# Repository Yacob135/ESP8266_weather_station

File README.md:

# ESP8266_weather_station

This weather station has an ESP8266-12F in combination with DS18B20 and/or BME280 for sensing. I used a TP4056 module for 18650 Li-Ion battery charging/protection and TPS63900 buck-boost converter, which has incredibly low quiescent current combined with great efficiency at low power consumption (>90% at 10uA).

The station connects to my local Blynk server and sends the data every 5 minutes. During deep-sleep the whole circuit consumes about 25uA, which is fantastic. It should last about a year on one charge, since it connects to my server, sends the data and goes back to sleep in about 0.7s on average (I used Blynk API to reduce the connection time). So the overall power consumption is really low.

Just a little warning when buying ESP8266-12F modules from aliexpress. Make sure to buy the Ai-Thinker version, since the "Espressif" version will have about 150uA in deep-sleep instead of 20uA. Learnt this the hard way.

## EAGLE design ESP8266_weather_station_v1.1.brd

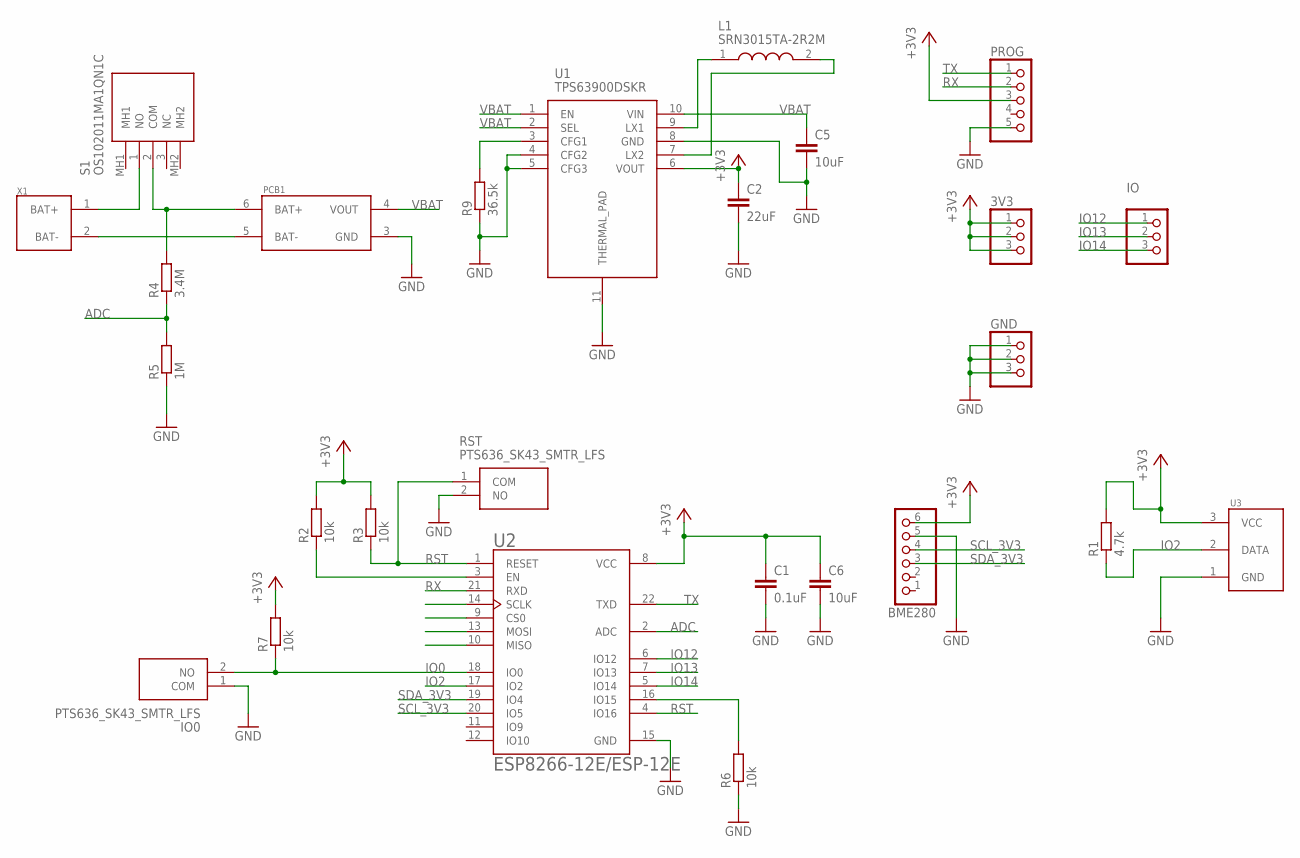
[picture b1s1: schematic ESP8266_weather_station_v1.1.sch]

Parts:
3V3: PINHD-1X3; 1X03
BME280: PINHD-1X6; 1X06
C1: 0.1uF; C0805
C2: 22uF; C0805
C5, C6: 10uF; C0805
GND: PINHD-1X3; 1X03
IO: PINHD-1X3; 1X03
IO0: PTS636_SK43_SMTR_LFS; PTS636SK43SMTRLFS
L1: SRN3015TA-2R2M; SRN3015TA2R2M
PCB1: TP4056_MODULE
PROG: PINHD-1X5; 1X05
R1: 4.7k; R0805
R2, R3, R6, R7: 10k; R0805
R4: 3.4M; R0805
R5: 1M; R0805
R9: 36.5k; R0805
RST: PTS636_SK43_SMTR_LFS; PTS636SK43SMTRLFS
S1: OS102011MA1QN1C
U1: TPS63900DSKR; SON50P250X250X80-11N
U2: ESP8266-12E/ESP-12E; XCVR_ESP8266-12E/ESP-12E
U3: DS18B20
X1: 18650_SMD_HOLDER

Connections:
+3V3: 3V3.1, 3V3.2, 3V3.3, BME280.6, C1.1, C2.1, C6.1, PROG.3, R1.2, R2.2, R3.2, R7.2, U1.6 (VOUT), U2.8 (VCC), U3.3 (VCC)
ADC: R4.1, R5.2, U2.2 (ADC)
GND: BME280.5, C1.2, C2.2, C5.2, C6.2, GND.1, GND.2, GND.3, IO0.1 (COM), PCB1.3 (GND), PROG.5, R5.1, R6.1, R9.1, RST.2 (NO), U1.4 (CFG2), U1.5 (CFG3), U1.8 (GND), U1.11 (THERMAL_PAD), U2.15 (GND), U3.1 (GND)
IO0: IO0.2 (NO), R7.1, U2.18 (IO0)
IO2: R1.1, U2.17 (IO2), U3.2 (DATA)
IO12: IO.1, U2.6 (IO12)
IO13: IO.2, U2.7 (IO13)
IO14: IO.3, U2.5 (IO14)
unnamed: S1.1 (NO), X1.1 (BAT+)
unnamed: R9.2, U1.3 (CFG1)
unnamed: PCB1.6 (BAT+), R4.2, S1.2 (COM)
unnamed: PCB1.5 (BAT-), X1.2 (BAT-)
unnamed: R6.2, U2.16 (IO15)
unnamed: L1.1, U1.9 (LX1)
unnamed: L1.2, U1.7 (LX2)
unnamed: R2.1, U2.3 (EN)
RST: R3.1, RST.1 (COM), U2.1 (RESET), U2.4 (IO16)
RX: PROG.2, U2.21 (RXD)
SCL_3V3: BME280.4, U2.20 (IO5)
SDA_3V3: BME280.3, U2.19 (IO4)
TX: PROG.1, U2.22 (TXD)
VBAT: C5.1, PCB1.4 (VOUT), U1.1 (EN), U1.2 (SEL), U1.10 (VIN)

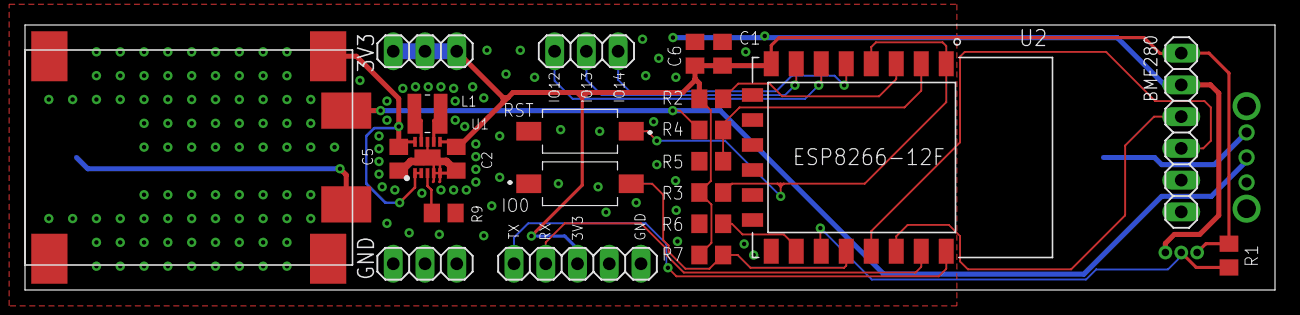
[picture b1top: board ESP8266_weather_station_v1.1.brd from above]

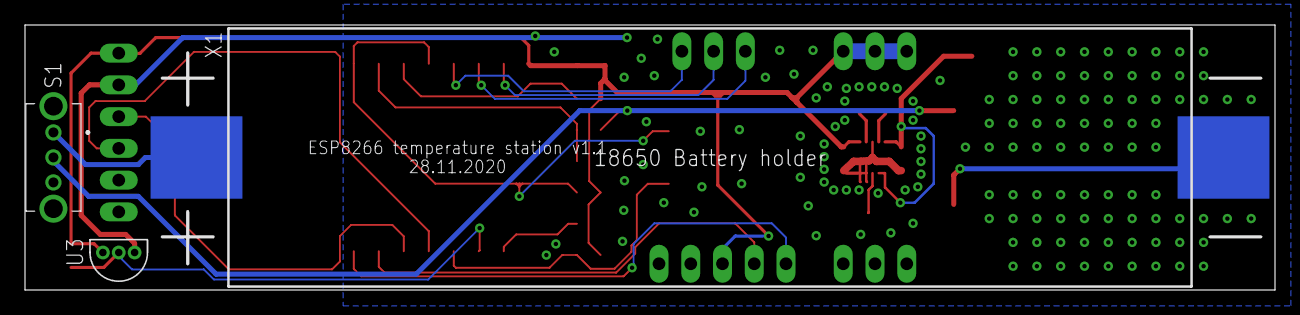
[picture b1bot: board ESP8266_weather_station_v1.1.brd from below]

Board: 2 copper layers, 100.0 x 21.2 mm, 26 parts (3 on the bottom side), 22 nets.
